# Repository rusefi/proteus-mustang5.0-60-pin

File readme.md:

Status: untested

See https://rusefi.com/forum/viewtopic.php?f=2&t=1890

[rev A schematics](https://github.com/rusefi/proteus-mustang5.0-60-pin/blob/main/boards/5.0mustangProteusPnP-a/board/5.0mustangProteusPnP-a-schematic.pdf)

[88 diagram](https://github.com/rusefi/rusefi/wiki/Ford-Fox-Body-(88-Ford-Mustang-302-V8))

# 5.0 Mustang Proteus PnP
PnP adapter board for 5.0 mustang EEC-IV computer using Proteus Rusefi v0.5 compatible board.

This board is designed as both a PnP stock replacement for the A9L/A9P EECs found in 5.0 manual foxbody mustangs, as well as a fully featured aftermarket ECU. This board is designed to fit into BOTH versions of the stock Ford EEC-IV case.

PLEASE do not rip apart any A9L computers to house this unit, there's very few of them left and they sell for a lot! Keep or sell that and buy any late 80s to early 90s EEC-IV as a donor instead such as 88 ford taurus 2.4 EEC for $25.

wiki and more info coming after fully tested.

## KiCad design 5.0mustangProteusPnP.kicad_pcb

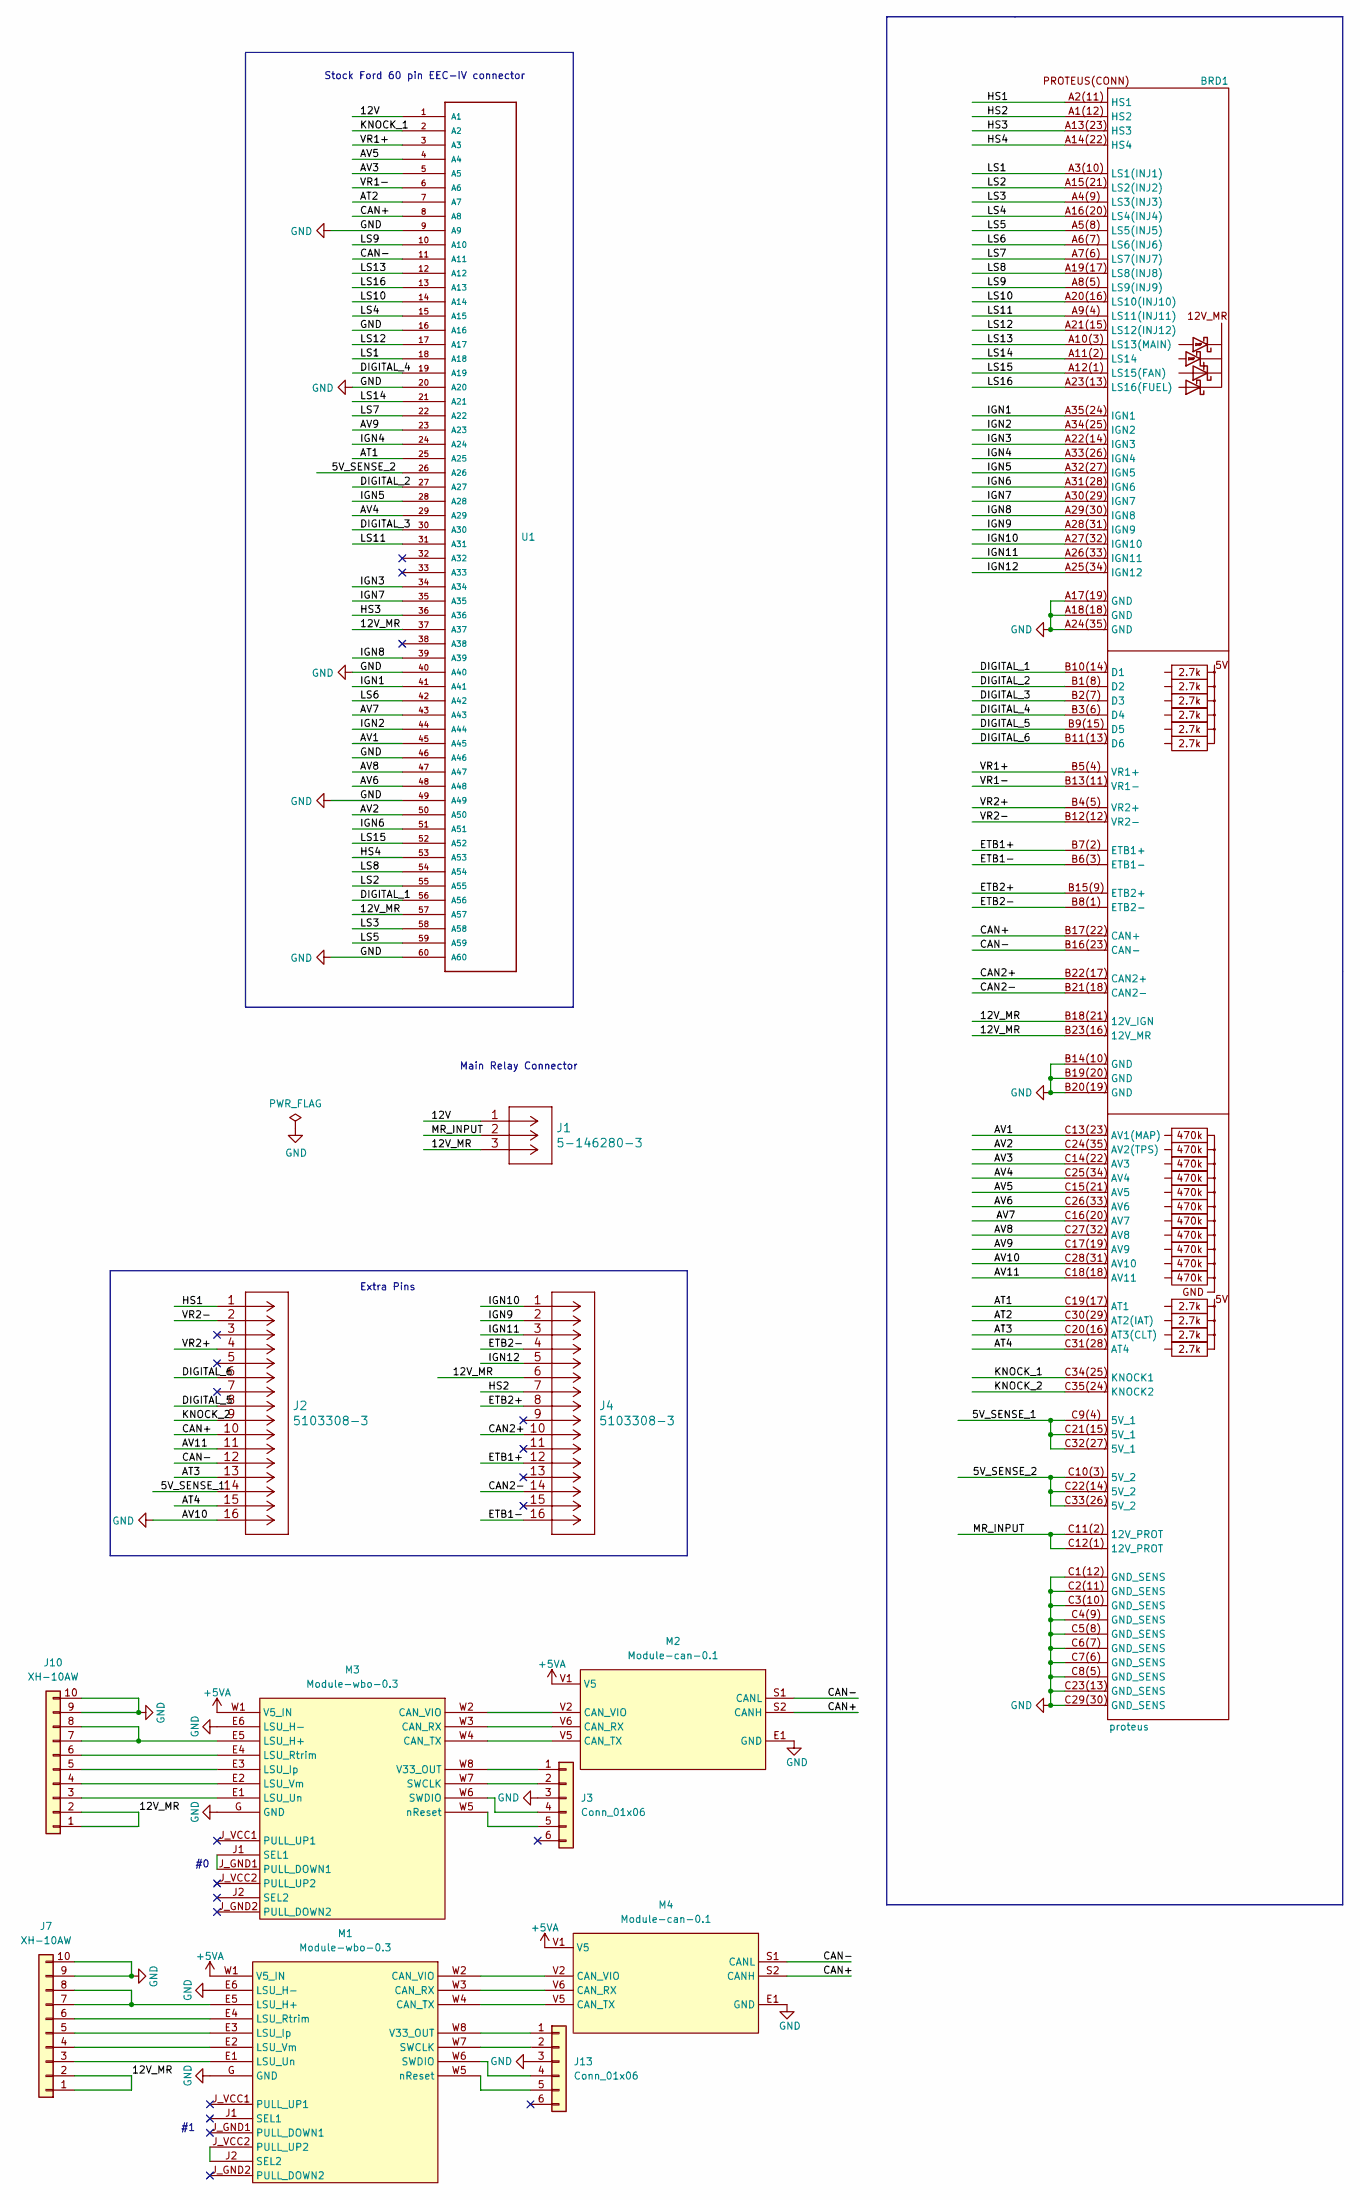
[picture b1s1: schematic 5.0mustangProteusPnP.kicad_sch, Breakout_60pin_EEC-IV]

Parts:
BRD1: proteus
J1: 5-146280-3
J2, J4: 5103308-3
J3, J13: Conn_01x06; PinHeader_1x06_P2.54mm_Vertical
J7, J10: XH-10AW; JST_XH_S10B-XH-A_1x10_P2.50mm_Horizontal; LCSC C14652
M1, M3: Module-wbo-0.3; wbo
M2, M4: Module-can-0.1; can
U1: FORD60PIN

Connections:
+5VA: M1.W1 (V5_IN), M2.V1 (V5), M3.W1 (V5_IN), M4.V1 (V5)
/5V_SENSE_1: BRD1.C9(4) (5V_1), BRD1.C21(15) (5V_1), BRD1.C32(27) (5V_1), J2.14
/5V_SENSE_2: BRD1.C10(3) (5V_2), BRD1.C22(14) (5V_2), BRD1.C33(26) (5V_2), U1.26 (A26)
/12V: J1.1, U1.1 (A1)
/12V_MR: BRD1.B18(21) (12V_IGN), BRD1.B23(16) (12V_MR), J1.3, J4.6, J7.1, J7.2, J10.1, J10.2, U1.37 (A37), U1.57 (A57)
/AT1: BRD1.C19(17) (AT1), U1.25 (A25)
/AT2: BRD1.C30(29) (AT2(IAT)), U1.7 (A7)
/AT3: BRD1.C20(16) (AT3(CLT)), J2.13
/AT4: BRD1.C31(28) (AT4), J2.15
/AV1: BRD1.C13(23) (AV1(MAP)), U1.45 (A45)
/AV2: BRD1.C24(35) (AV2(TPS)), U1.50 (A50)
/AV3: BRD1.C14(22) (AV3), U1.5 (A5)
/AV4: BRD1.C25(34) (AV4), U1.29 (A29)
/AV5: BRD1.C15(21) (AV5), U1.4 (A4)
/AV6: BRD1.C26(33) (AV6), U1.48 (A48)
/AV7: BRD1.C16(20) (AV7), U1.43 (A43)
/AV8: BRD1.C27(32) (AV8), U1.47 (A47)
/AV9: BRD1.C17(19) (AV9), U1.23 (A23)
/AV11: BRD1.C18(18) (AV11), J2.11
/CAN2+: BRD1.B22(17) (CAN2+), J4.10
/CAN2-: BRD1.B21(18) (CAN2-), J4.14
/CAN+: BRD1.B17(22) (CAN+), J2.10, M2.S2 (CANH), M4.S2 (CANH), U1.8 (A8)
/CAN-: BRD1.B16(23) (CAN-), J2.12, M2.S1 (CANL), M4.S1 (CANL), U1.11 (A11)
/DIGITAL_1: BRD1.B10(14) (D1), U1.56 (A56)
/DIGITAL_2: BRD1.B1(8) (D2), U1.27 (A27)
/DIGITAL_3: BRD1.B2(7) (D3), U1.30 (A30)
/DIGITAL_4: BRD1.B3(6) (D4), U1.19 (A19)
/DIGITAL_5: BRD1.B9(15) (D5), J2.8
/DIGITAL_6: BRD1.B11(13) (D6), J2.6
/ETB1+: BRD1.B7(2) (ETB1+), J4.12
/ETB1-: BRD1.B6(3) (ETB1-), J4.16
/ETB2+: BRD1.B15(9) (ETB2+), J4.8
/ETB2-: BRD1.B8(1) (ETB2-), J4.4
/HS1: BRD1.A2(11) (HS1), J2.1
/HS2: BRD1.A1(12) (HS2), J4.7
/HS3: BRD1.A13(23) (HS3), U1.36 (A36)
/HS4: BRD1.A14(22) (HS4), U1.53 (A53)
/IGN1: BRD1.A35(24) (IGN1), U1.41 (A41)
/IGN2: BRD1.A34(25) (IGN2), U1.44 (A44)
/IGN3: BRD1.A22(14) (IGN3), U1.34 (A34)
/IGN4: BRD1.A33(26) (IGN4), U1.24 (A24)
/IGN5: BRD1.A32(27) (IGN5), U1.28 (A28)
/IGN6: BRD1.A31(28) (IGN6), U1.51 (A51)
/IGN7: BRD1.A30(29) (IGN7), U1.35 (A35)
/IGN8: BRD1.A29(30) (IGN8), U1.39 (A39)
/IGN9: BRD1.A28(31) (IGN9), J4.2
/IGN10: BRD1.A27(32) (IGN10), J4.1
/IGN11: BRD1.A26(33) (IGN11), J4.3
/IGN12: BRD1.A25(34) (IGN12), J4.5
/KNOCK_1: BRD1.C34(25) (KNOCK1), U1.2 (A2)
/KNOCK_2: BRD1.C35(24) (KNOCK2), J2.9
/LS1: BRD1.A3(10) (LS1(INJ1)), U1.18 (A18)
/LS2: BRD1.A15(21) (LS2(INJ2)), U1.55 (A55)
/LS3: BRD1.A4(9) (LS3(INJ3)), U1.58 (A58)
/LS4: BRD1.A16(20) (LS4(INJ4)), U1.15 (A15)
/LS5: BRD1.A5(8) (LS5(INJ5)), U1.59 (A59)
/LS6: BRD1.A6(7) (LS6(INJ6)), U1.42 (A42)
/LS7: BRD1.A7(6) (LS7(INJ7)), U1.22 (A22)
/LS8: BRD1.A19(17) (LS8(INJ8)), U1.54 (A54)
/LS9: BRD1.A8(5) (LS9(INJ9)), U1.10 (A10)
/LS10: BRD1.A20(16) (LS10(INJ10)), U1.14 (A14)
/LS11: BRD1.A9(4) (LS11(INJ11)), U1.31 (A31)
/LS12: BRD1.A21(15) (LS12(INJ12)), U1.17 (A17)
/LS13: BRD1.A10(3) (LS13(MAIN)), U1.12 (A12)
/LS14: BRD1.A11(2) (LS14), U1.21 (A21)
/LS15: BRD1.A12(1) (LS15(FAN)), U1.52 (A52)
/LS16: BRD1.A23(13) (LS16(FUEL)), U1.13 (A13)
/MR_INPUT: BRD1.C11(2) (12V_PROT), BRD1.C12(1) (12V_PROT), J1.2
/VR1+: BRD1.B5(4) (VR1+), U1.3 (A3)
/VR1-: BRD1.B13(11) (VR1-), U1.6 (A6)
/VR2+: BRD1.B4(5) (VR2+), J2.4
/VR2-: BRD1.B12(12) (VR2-), J2.2
GND: BRD1.A17(19) (GND), BRD1.A18(18) (GND), BRD1.A24(35) (GND), BRD1.B14(10) (GND), BRD1.B19(20) (GND), BRD1.B20(19) (GND), BRD1.C1(12) (GND_SENS), BRD1.C2(11) (GND_SENS), BRD1.C3(10) (GND_SENS), BRD1.C4(9) (GND_SENS), BRD1.C5(8) (GND_SENS), BRD1.C6(7) (GND_SENS), BRD1.C7(6) (GND_SENS), BRD1.C8(5) (GND_SENS), BRD1.C23(13) (GND_SENS), BRD1.C28(31) (AV10), BRD1.C29(30) (GND_SENS), J2.16, J3.3, J7.9, J7.10, J10.9, J10.10, J13.3, M1.E6 (LSU_H-), M1.G (GND), M2.E1 (GND), M3.E6 (LSU_H-), M3.G (GND), M4.E1 (GND), U1.9 (A9), U1.16 (A16), U1.20 (A20), U1.40 (A40), U1.46 (A46), U1.49 (A49), U1.60 (A60)
unnamed: J3.1, M3.W8 (V33_OUT)
unnamed: J3.2, M3.W7 (SWCLK)
unnamed: J3.4, M3.W6 (SWDIO)
unnamed: J3.5, M3.W5 (nReset)
unnamed: J7.3, M1.E1 (LSU_Un)
unnamed: J7.4, M1.E2 (LSU_Vm)
unnamed: J7.5, M1.E3 (LSU_Ip)
unnamed: J7.6, M1.E4 (LSU_Rtrim)
unnamed: J7.7, J7.8, M1.E5 (LSU_H+)
unnamed: J10.3, M3.E1 (LSU_Un)
unnamed: J10.4, M3.E2 (LSU_Vm)
unnamed: J10.5, M3.E3 (LSU_Ip)
unnamed: J10.6, M3.E4 (LSU_Rtrim)
unnamed: J10.7, J10.8, M3.E5 (LSU_H+)
unnamed: J13.1, M1.W8 (V33_OUT)
unnamed: J13.2, M1.W7 (SWCLK)
unnamed: J13.4, M1.W6 (SWDIO)
unnamed: J13.5, M1.W5 (nReset)
unnamed: M1.J2 (SEL2), M1.J_VCC2 (PULL_UP2)
unnamed: M1.W2 (CAN_VIO), M4.V2 (CAN_VIO)
unnamed: M1.W3 (CAN_RX), M4.V6 (CAN_RX)
unnamed: M1.W4 (CAN_TX), M4.V5 (CAN_TX)
unnamed: M2.V2 (CAN_VIO), M3.W2 (CAN_VIO)
unnamed: M2.V5 (CAN_TX), M3.W4 (CAN_TX)
unnamed: M2.V6 (CAN_RX), M3.W3 (CAN_RX)
unnamed: M3.J1 (SEL1), M3.J_GND1 (PULL_DOWN1)

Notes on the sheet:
Stock Ford 60 pin EEC-IV connector
Extra Pins
Main Relay Connector

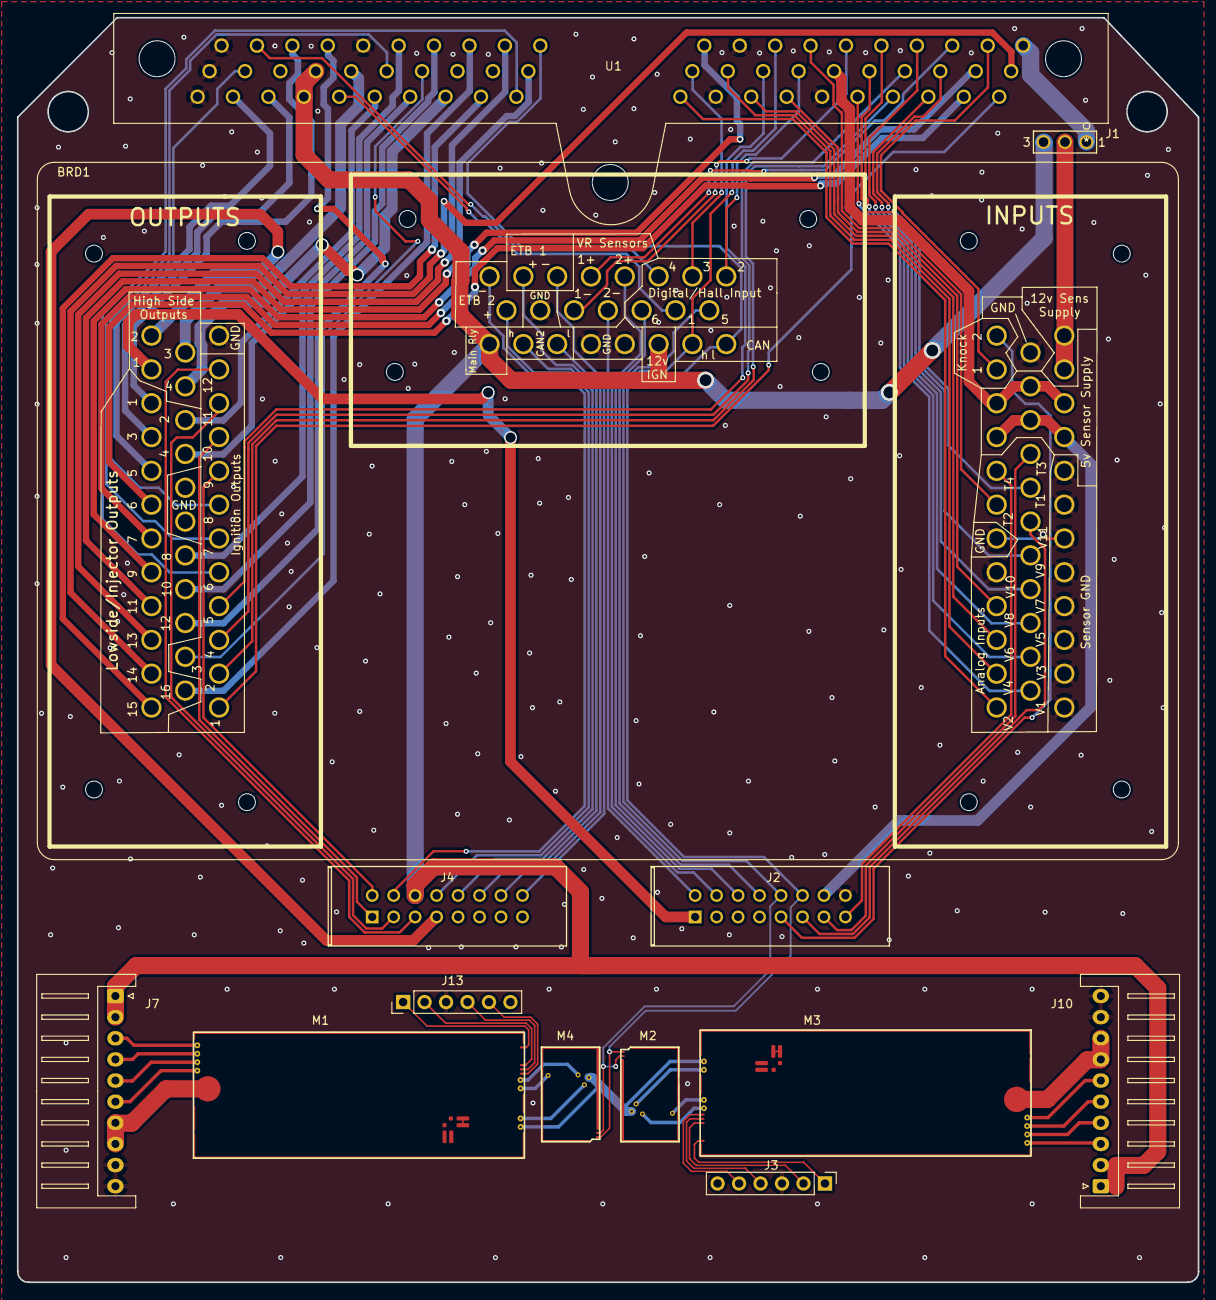
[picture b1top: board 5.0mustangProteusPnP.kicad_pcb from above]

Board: 2 copper layers, 139.7 x 149.6 mm, 13 parts (0 on the bottom side), 99 nets.

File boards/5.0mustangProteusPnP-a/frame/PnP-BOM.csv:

Comment,Designator,Footprint,LCSC Part #
"proteus","BRD1","proteus",""
"5-146280-3","J1","5-146280-3",""
"5103308-3","J2","5103308-3",""
"Conn_01x06","J3","PinHeader_1x06_P2.54mm_Vertical",""
"5103308-3","J4","5103308-3",""
"XH-10AW","J7","JST_XH_S10B-XH-A_1x10_P2.50mm_Horizontal","C14652"
"XH-10AW","J10","JST_XH_S10B-XH-A_1x10_P2.50mm_Horizontal","C14652"
"Conn_01x06","J13","PinHeader_1x06_P2.54mm_Vertical",""
"Module:wbo/0.3","M1","wbo",""
"Module:can/0.1","M2","can",""
"Module:wbo/0.3","M3","wbo",""
"Module:can/0.1","M4","can",""
"FORD60PIN","U1","FORD60PIN",""

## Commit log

2021-10-28 ignoring backups
2022-03-30 .pdf
2022-04-14 hellen-one
2022-05-12 update
    обновила до 6.0, поставила современный футпринт
2022-05-15 add WBO module in sch
2022-05-17 трассировка
2022-05-18 progress
2022-05-19 add export files
2022-05-23 proper folder name
2022-05-23 fresh
2022-05-23 proper folder name x2
2022-05-26 new outputs
2022-05-26 axes
    изменила направление отчета по оси ординат
2022-05-27 latest
2022-05-29 new gerbers
2022-05-29 Auto-generated board
2022-06-06 я пробую свои теории
    с абсолютным началом
2022-06-06 new gerbes
    Эта ревизия с проставленным началом координат. Странная конечно прога, имеющая три свои сетки одновременно :)
2022-06-06 size board
2022-06-07 replace progress

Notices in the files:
parts and their libraries:
Copyright 2016 Accelerated Designs. All rights reserved.
